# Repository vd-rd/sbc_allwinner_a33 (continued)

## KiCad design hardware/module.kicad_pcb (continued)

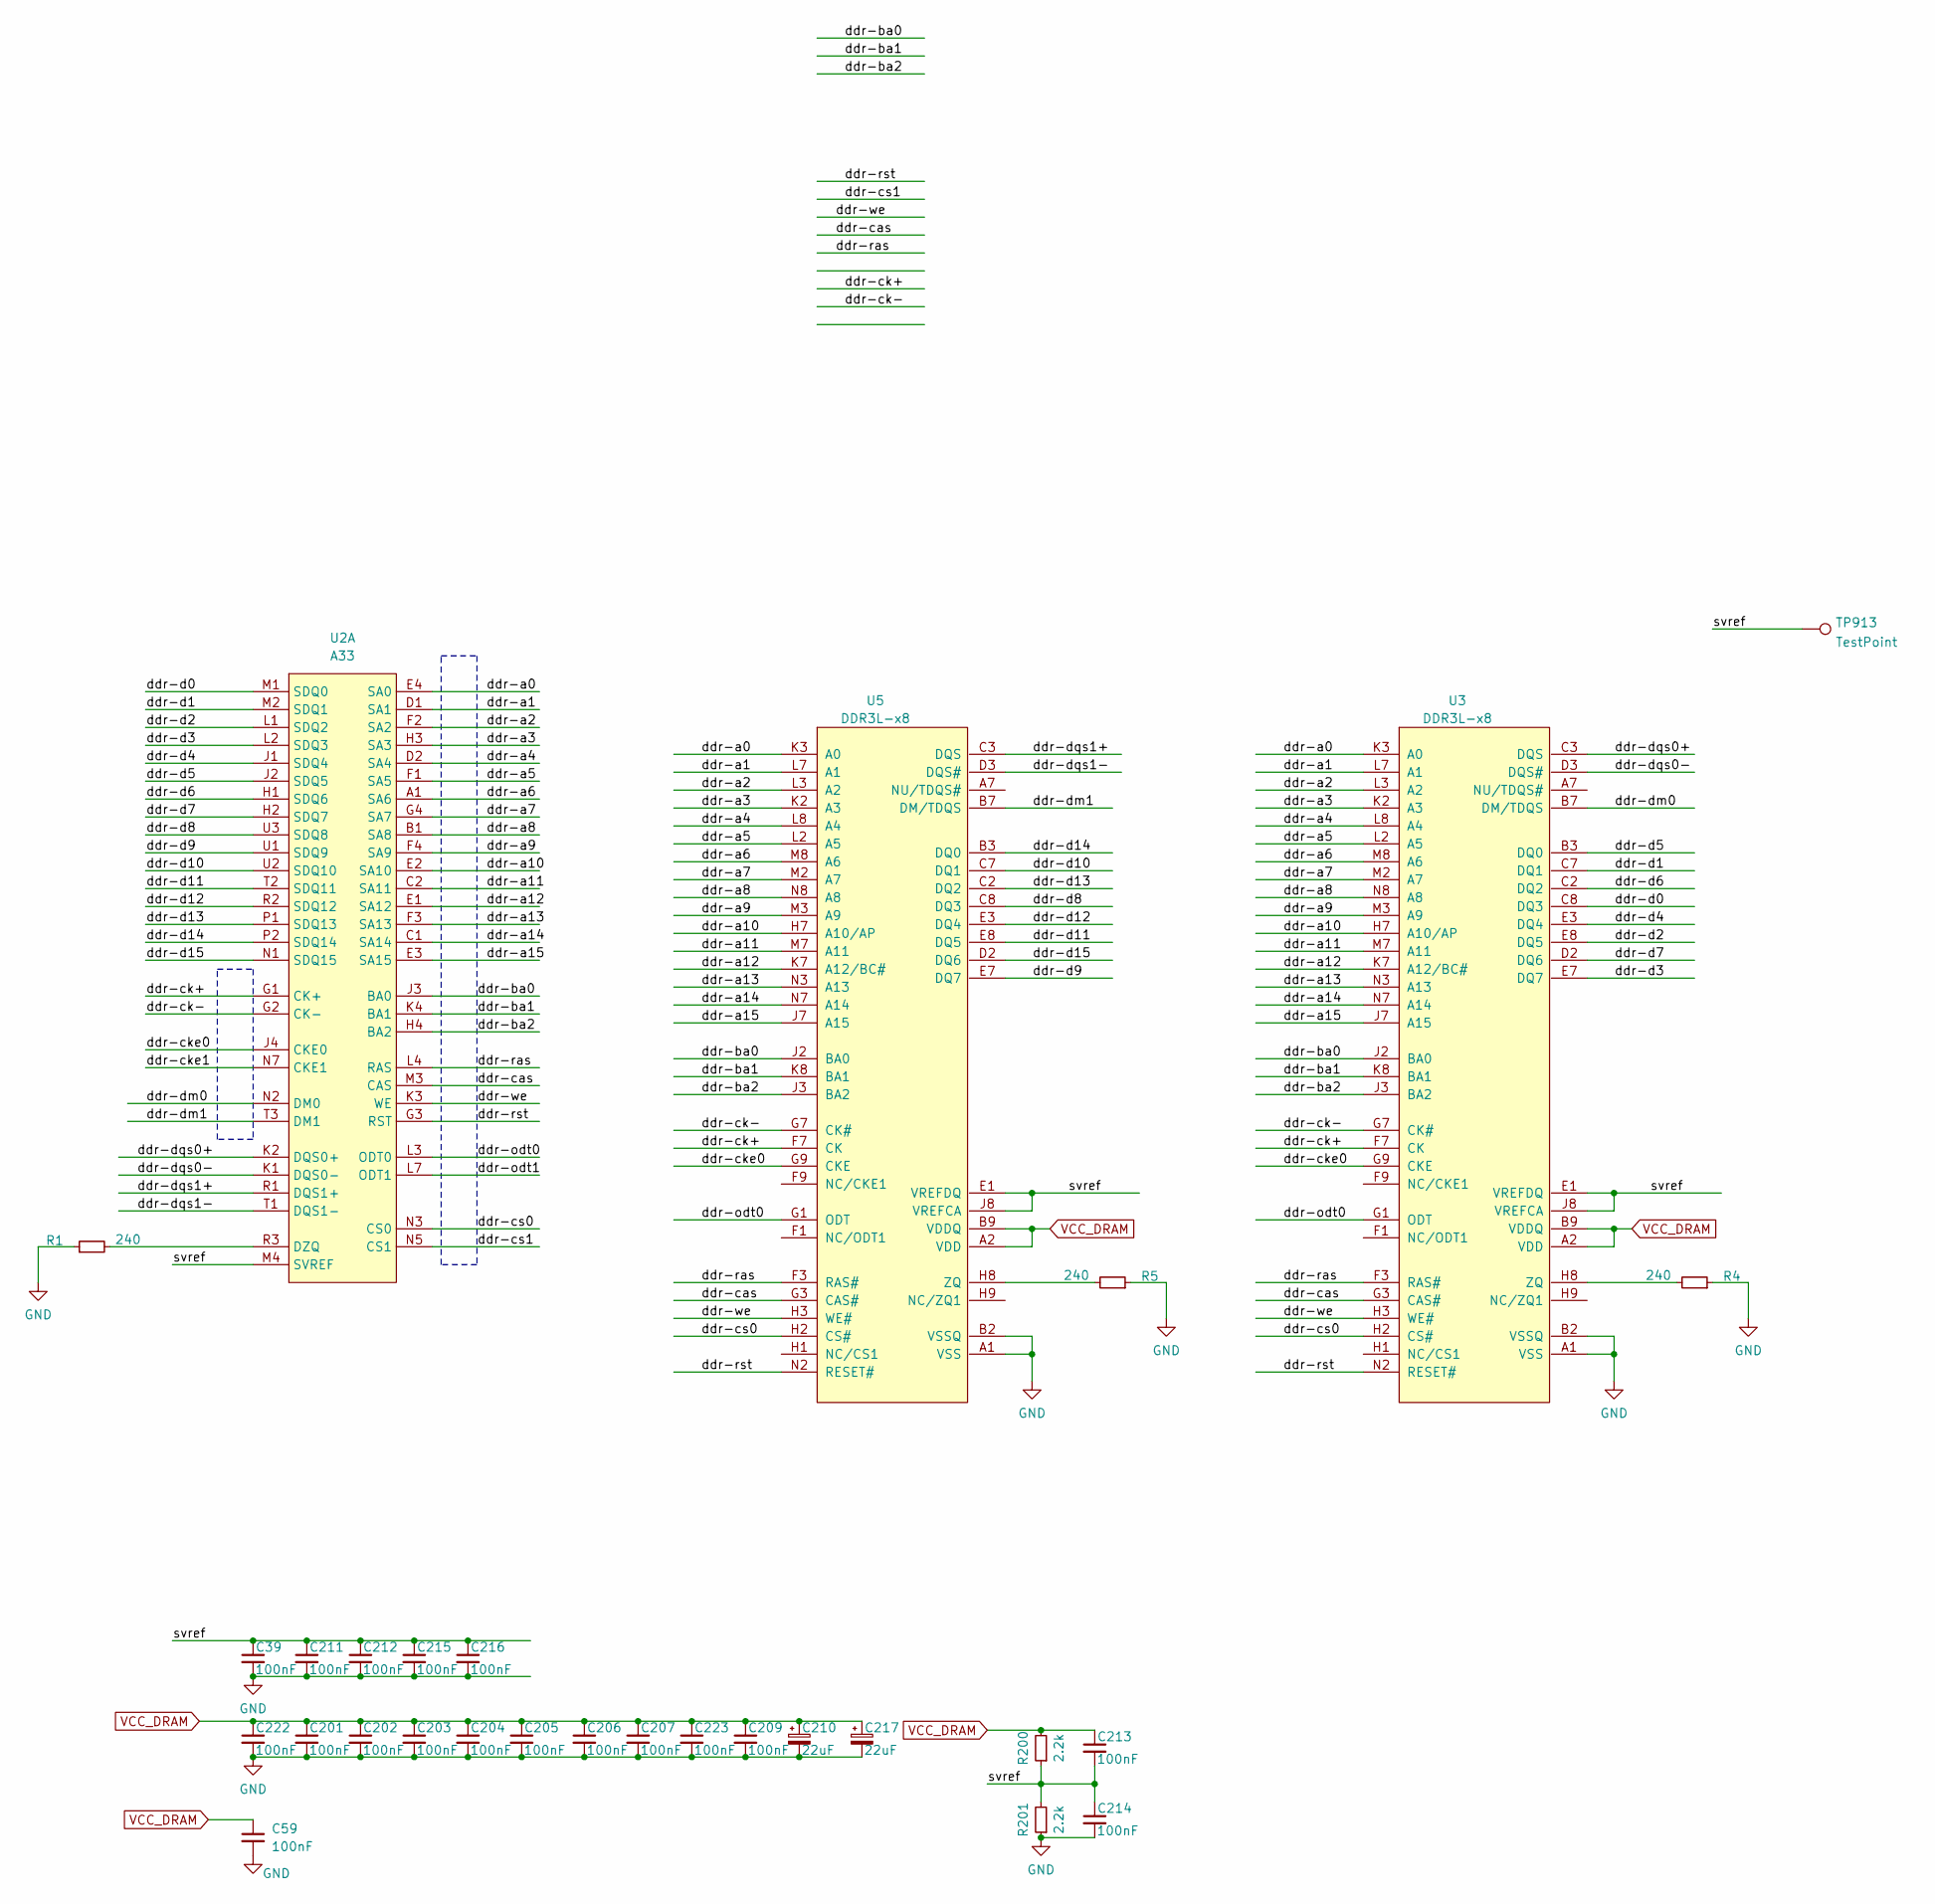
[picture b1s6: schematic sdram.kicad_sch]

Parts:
C39, C59, C201, C202, C203, C204, C205, C206, C207, C209, C211, C212, C213, C214, C215, C216, C222, C223: 100nF; C_0402_1005Metric
C210, C217: 22uF; CP_EIA-2012-15_AVX-P
R1, R4, R5: 240; R_0402_1005Metric
R200, R201: 2.2k; R_0402_1005Metric
TP913: TestPoint; TestPoint_Pad_D1.0mm
U2: A33; BGA-282_17x17_14.0x14.0mm
U3, U5: DDR3L-x8; BGA-78_9x13_9.0x10.5mm

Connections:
/DDR3 Memory/ddr-a0: U2.E4 (SA0), U3.K3 (A0), U5.K3 (A0)
/DDR3 Memory/ddr-a1: U2.D1 (SA1), U3.L7 (A1), U5.L7 (A1)
/DDR3 Memory/ddr-a2: U2.F2 (SA2), U3.L3 (A2), U5.L3 (A2)
/DDR3 Memory/ddr-a3: U2.H3 (SA3), U3.K2 (A3), U5.K2 (A3)
/DDR3 Memory/ddr-a4: U2.D2 (SA4), U3.L8 (A4), U5.L8 (A4)
/DDR3 Memory/ddr-a5: U2.F1 (SA5), U3.L2 (A5), U5.L2 (A5)
/DDR3 Memory/ddr-a6: U2.A1 (SA6), U3.M8 (A6), U5.M8 (A6)
/DDR3 Memory/ddr-a7: U2.G4 (SA7), U3.M2 (A7), U5.M2 (A7)
/DDR3 Memory/ddr-a8: U2.B1 (SA8), U3.N8 (A8), U5.N8 (A8)
/DDR3 Memory/ddr-a9: U2.F4 (SA9), U3.M3 (A9), U5.M3 (A9)
/DDR3 Memory/ddr-a10: U2.E2 (SA10), U3.H7 (A10/AP), U5.H7 (A10/AP)
/DDR3 Memory/ddr-a11: U2.C2 (SA11), U3.M7 (A11), U5.M7 (A11)
/DDR3 Memory/ddr-a12: U2.E1 (SA12), U3.K7 (A12/BC#), U5.K7 (A12/BC#)
/DDR3 Memory/ddr-a13: U2.F3 (SA13), U3.N3 (A13), U5.N3 (A13)
/DDR3 Memory/ddr-a14: U2.C1 (SA14), U3.N7 (A14), U5.N7 (A14)
/DDR3 Memory/ddr-a15: U2.E3 (SA15), U3.J7 (A15), U5.J7 (A15)
/DDR3 Memory/ddr-ba0: U2.J3 (BA0), U3.J2 (BA0), U5.J2 (BA0)
/DDR3 Memory/ddr-ba1: U2.K4 (BA1), U3.K8 (BA1), U5.K8 (BA1)
/DDR3 Memory/ddr-ba2: U2.H4 (BA2), U3.J3 (BA2), U5.J3 (BA2)
/DDR3 Memory/ddr-cas: U2.M3 (CAS), U3.G3 (CAS#), U5.G3 (CAS#)
/DDR3 Memory/ddr-ck+: U2.G1 (CK+), U3.F7 (CK), U5.F7 (CK)
/DDR3 Memory/ddr-ck-: U2.G2 (CK-), U3.G7 (CK#), U5.G7 (CK#)
/DDR3 Memory/ddr-cke0: U2.J4 (CKE0), U3.G9 (CKE), U5.G9 (CKE)
/DDR3 Memory/ddr-cke1: U2.N7 (CKE1)
/DDR3 Memory/ddr-cs0: U2.N3 (CS0), U3.H2 (CS#), U5.H2 (CS#)
/DDR3 Memory/ddr-cs1: U2.N5 (CS1)
/DDR3 Memory/ddr-d0: U2.M1 (SDQ0), U3.C8 (DQ3)
/DDR3 Memory/ddr-d1: U2.M2 (SDQ1), U3.C7 (DQ1)
/DDR3 Memory/ddr-d2: U2.L1 (SDQ2), U3.E8 (DQ5)
/DDR3 Memory/ddr-d3: U2.L2 (SDQ3), U3.E7 (DQ7)
/DDR3 Memory/ddr-d4: U2.J1 (SDQ4), U3.E3 (DQ4)
/DDR3 Memory/ddr-d5: U2.J2 (SDQ5), U3.B3 (DQ0)
/DDR3 Memory/ddr-d6: U2.H1 (SDQ6), U3.C2 (DQ2)
/DDR3 Memory/ddr-d7: U2.H2 (SDQ7), U3.D2 (DQ6)
/DDR3 Memory/ddr-d8: U2.U3 (SDQ8), U5.C8 (DQ3)
/DDR3 Memory/ddr-d9: U2.U1 (SDQ9), U5.E7 (DQ7)
/DDR3 Memory/ddr-d10: U2.U2 (SDQ10), U5.C7 (DQ1)
/DDR3 Memory/ddr-d11: U2.T2 (SDQ11), U5.E8 (DQ5)
/DDR3 Memory/ddr-d12: U2.R2 (SDQ12), U5.E3 (DQ4)
/DDR3 Memory/ddr-d13: U2.P1 (SDQ13), U5.C2 (DQ2)
/DDR3 Memory/ddr-d14: U2.P2 (SDQ14), U5.B3 (DQ0)
/DDR3 Memory/ddr-d15: U2.N1 (SDQ15), U5.D2 (DQ6)
/DDR3 Memory/ddr-dm0: U2.N2 (DM0), U3.B7 (DM/TDQS)
/DDR3 Memory/ddr-dm1: U2.T3 (DM1), U5.B7 (DM/TDQS)
/DDR3 Memory/ddr-dqs0+: U2.K2 (DQS0+), U3.C3 (DQS)
/DDR3 Memory/ddr-dqs0-: U2.K1 (DQS0-), U3.D3 (DQS#)
/DDR3 Memory/ddr-dqs1+: U2.R1 (DQS1+), U5.C3 (DQS)
/DDR3 Memory/ddr-dqs1-: U2.T1 (DQS1-), U5.D3 (DQS#)
/DDR3 Memory/ddr-odt0: U2.L3 (ODT0), U3.G1 (ODT), U5.G1 (ODT)
/DDR3 Memory/ddr-odt1: U2.L7 (ODT1)
/DDR3 Memory/ddr-ras: U2.L4 (RAS), U3.F3 (RAS#), U5.F3 (RAS#)
/DDR3 Memory/ddr-rst: U2.G3 (RST), U3.N2 (RESET#), U5.N2 (RESET#)
/DDR3 Memory/ddr-we: U2.K3 (WE), U3.H3 (WE#), U5.H3 (WE#)
/DDR3 Memory/svref: C39.1, C211.1, C212.1, C213.2, C214.1, C215.1, C216.1, R200.1, R201.2, TP913.1 (1_1), U2.M4 (SVREF), U3.E1 (VREFDQ), U3.J8 (VREFCA), U5.E1 (VREFDQ), U5.J8 (VREFCA)
GND: C39.2, C59.2, C201.2, C202.2, C203.2, C204.2, C205.2, C206.2, C207.2, C209.2, C210.2, C211.2, C212.2, C214.2, C215.2, C216.2, C217.2, C222.2, C223.2, R1.1, R4.1, R5.1, R201.1, U3.A1 (VSS), U3.A8 (VSS), U3.B1 (VSS), U3.B2 (VSSQ), U3.B8 (VSSQ), U3.C9 (VSSQ), U3.D1 (VSSQ), U3.D8 (VSS), U3.D9 (VSSQ), U3.F2 (VSS), U3.F8 (VSS), U3.J1 (VSS), U3.J9 (VSS), U3.L1 (VSS), U3.L9 (VSS), U3.N1 (VSS), U3.N9 (VSS), U5.A1 (VSS), U5.A8 (VSS), U5.B1 (VSS), U5.B2 (VSSQ), U5.B8 (VSSQ), U5.C9 (VSSQ), U5.D1 (VSSQ), U5.D8 (VSS), U5.D9 (VSSQ), U5.F2 (VSS), U5.F8 (VSS), U5.J1 (VSS), U5.J9 (VSS), U5.L1 (VSS), U5.L9 (VSS), U5.N1 (VSS), U5.N9 (VSS); also elsewhere on the board
unnamed: R1.2, U2.R3 (DZQ)
unnamed: R4.2, U3.H8 (ZQ)
unnamed: R5.2, U5.H8 (ZQ)
VCC_DRAM: C59.1, C201.1, C202.1, C203.1, C204.1, C205.1, C206.1, C207.1, C209.1, C210.1, C213.1, C217.1, C222.1, C223.1, R200.2, U3.A2 (VDD), U3.A9 (VDD), U3.B9 (VDDQ), U3.C1 (VDDQ), U3.D7 (VDD), U3.E2 (VDDQ), U3.E9 (VDDQ), U3.G2 (VDD), U3.G8 (VDD), U3.K1 (VDD), U3.K9 (VDD), U3.M1 (VDD), U3.M9 (VDD), U5.A2 (VDD), U5.A9 (VDD), U5.B9 (VDDQ), U5.C1 (VDDQ), U5.D7 (VDD), U5.E2 (VDDQ), U5.E9 (VDDQ), U5.G2 (VDD), U5.G8 (VDD), U5.K1 (VDD), U5.K9 (VDD), U5.M1 (VDD), U5.M9 (VDD); also elsewhere on the board

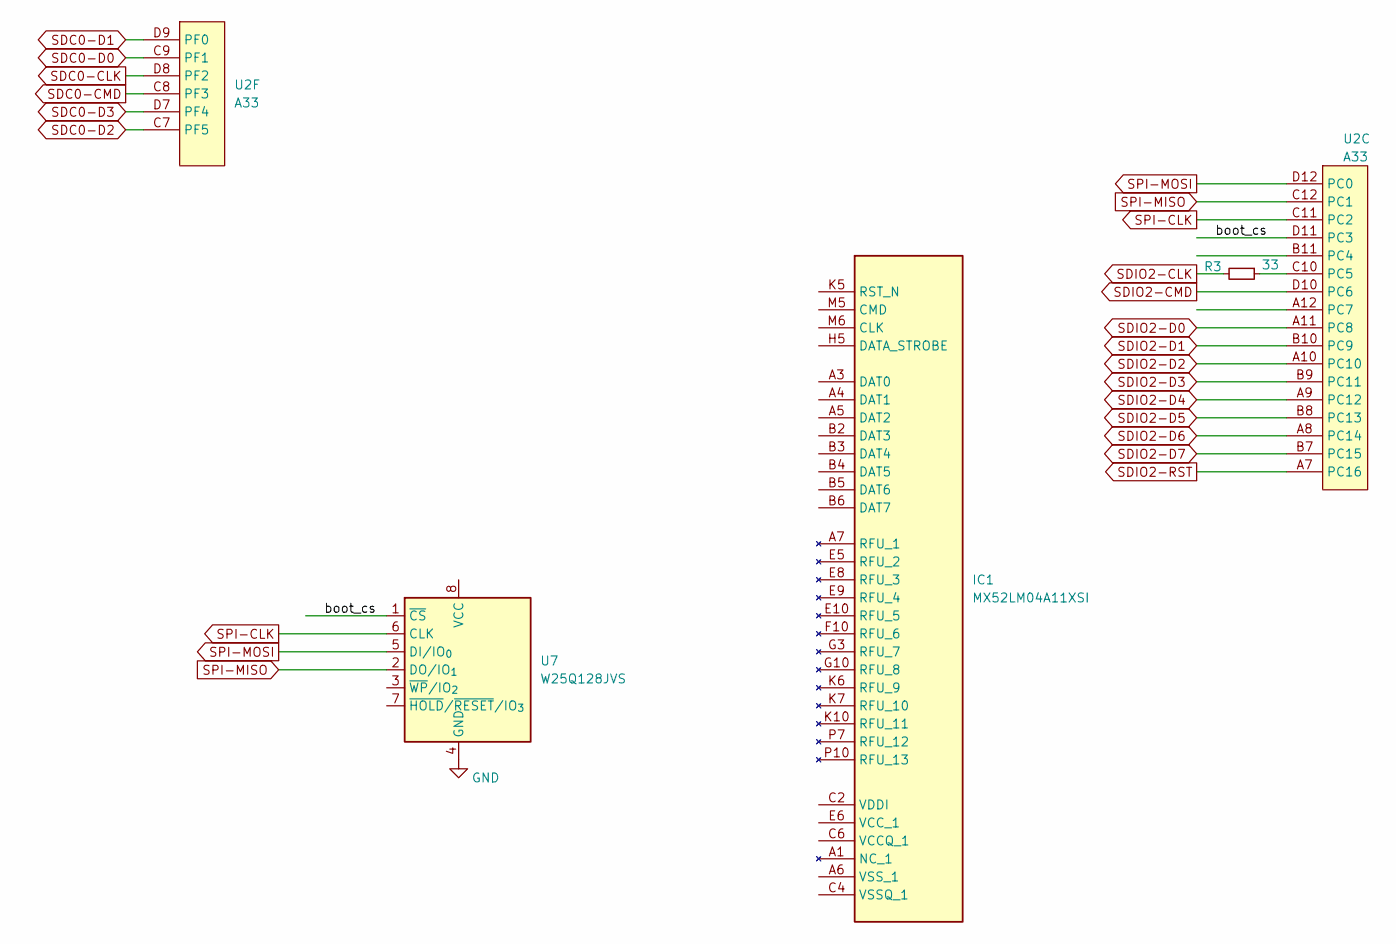
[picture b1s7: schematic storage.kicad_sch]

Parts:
IC1: MX52LM04A11XSI; BGA153C50P14X14_1150X1300X80; Mouser Part Number 95-52LM04A11XSIT
R3: 33; R_0402_1005Metric
U2: A33; BGA-282_17x17_14.0x14.0mm
U7: W25Q128JVS; SOIC-8_5.3x5.3mm_P1.27mm

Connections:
/Storage/boot_cs: U2.D11 (PC3), U7.1 (~CS)
GND: U7.4 (GND); also elsewhere on the board
unnamed: IC1.C6 (VCCQ_1), IC1.M4 (VCCQ_2), IC1.N4 (VCCQ_3), IC1.P3 (VCCQ_4), IC1.P5 (VCCQ_5)
unnamed: IC1.E6 (VCC_1), IC1.F5 (VCC_2), IC1.J10 (VCC_3), IC1.K9 (VCC_4)
unnamed: IC1.C4 (VSSQ_1), IC1.N2 (VSSQ_2), IC1.N5 (VSSQ_3), IC1.P4 (VSSQ_4), IC1.P6 (VSSQ_5)
unnamed: IC1.A6 (VSS_1), IC1.E7 (VSS_2), IC1.G5 (VSS_3), IC1.H10 (VSS_4), IC1.J5 (VSS_5), IC1.K8 (VSS_6)
unnamed: R3.1, U2.C10 (PC5)
SDC0-CLK: U2.D8 (PF2); also elsewhere on the board
SDC0-CMD: U2.C8 (PF3); also elsewhere on the board
SDC0-D0: U2.C9 (PF1); also elsewhere on the board
SDC0-D1: U2.D9 (PF0); also elsewhere on the board
SDC0-D2: U2.C7 (PF5); also elsewhere on the board
SDC0-D3: U2.D7 (PF4); also elsewhere on the board
SDIO2-CLK: R3.2
SDIO2-CMD: U2.D10 (PC6)
SDIO2-D0: U2.A11 (PC8)
SDIO2-D1: U2.B10 (PC9)
SDIO2-D2: U2.A10 (PC10)
SDIO2-D3: U2.B9 (PC11)
SDIO2-D4: U2.A9 (PC12)
SDIO2-D5: U2.B8 (PC13)
SDIO2-D6: U2.A8 (PC14)
SDIO2-D7: U2.B7 (PC15)
SDIO2-RST: U2.A7 (PC16)
SPI-CLK: U2.C11 (PC2), U7.6 (CLK); also elsewhere on the board
SPI-MISO: U2.C12 (PC1), U7.2 (DO/IO_{1}); also elsewhere on the board
SPI-MOSI: U2.D12 (PC0), U7.5 (DI/IO_{0}); also elsewhere on the board

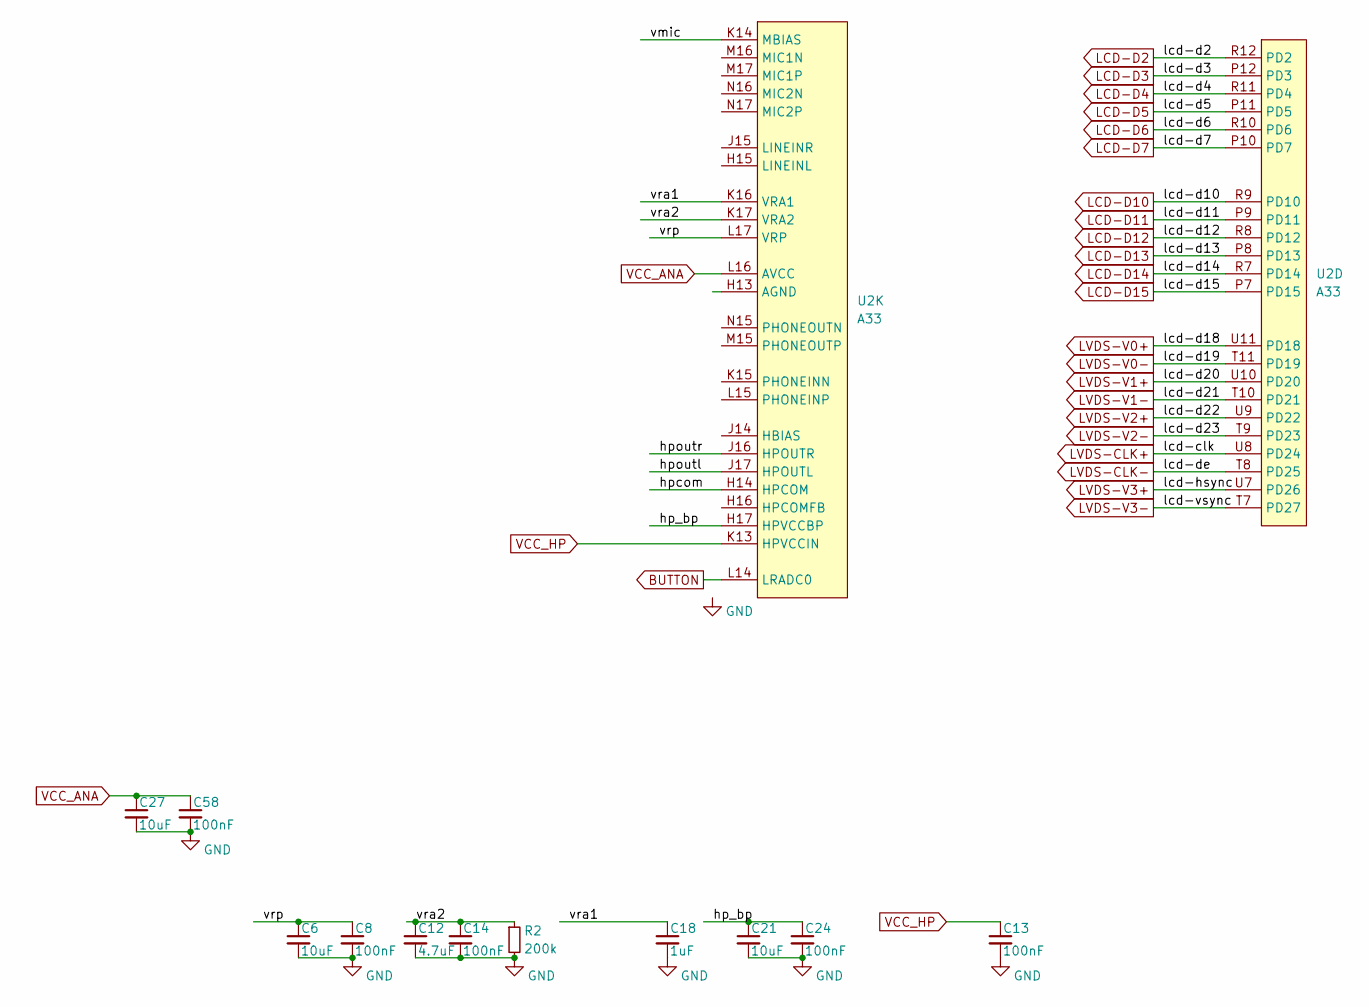
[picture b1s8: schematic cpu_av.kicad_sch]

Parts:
C6, C21, C27: 10uF; C_0603_1608Metric
C8, C13, C14, C24, C58: 100nF; C_0402_1005Metric
C12: 4.7uF; C_0603_1608Metric
C18: 1uF; C_0402_1005Metric
R2: 200k; R_0402_1005Metric
U2: A33; BGA-282_17x17_14.0x14.0mm

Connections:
/AudioVideo/hp_bp: C21.1, C24.1, U2.H17 (HPVCCBP)
/AudioVideo/hpcom: U2.H14 (HPCOM)
/AudioVideo/hpoutl: U2.J17 (HPOUTL)
/AudioVideo/hpoutr: U2.J16 (HPOUTR)
/AudioVideo/vmic: U2.K14 (MBIAS)
/AudioVideo/vra1: C18.1, U2.K16 (VRA1)
/AudioVideo/vra2: C12.1, C14.1, R2.1, U2.K17 (VRA2)
/AudioVideo/vrp: C6.1, C8.1, U2.L17 (VRP)
BUTTON: U2.L14 (LRADC0); also elsewhere on the board
GND: C6.2, C8.2, C12.2, C13.2, C14.2, C18.2, C21.2, C24.2, C27.2, C58.2, R2.2; also elsewhere on the board
LCD-D2: U2.R12 (PD2); also elsewhere on the board
LCD-D3: U2.P12 (PD3); also elsewhere on the board
LCD-D4: U2.R11 (PD4); also elsewhere on the board
LCD-D5: U2.P11 (PD5); also elsewhere on the board
LCD-D6: U2.R10 (PD6); also elsewhere on the board
LCD-D7: U2.P10 (PD7); also elsewhere on the board
LCD-D10: U2.R9 (PD10); also elsewhere on the board
LCD-D11: U2.P9 (PD11); also elsewhere on the board
LCD-D12: U2.R8 (PD12); also elsewhere on the board
LCD-D13: U2.P8 (PD13); also elsewhere on the board
LCD-D14: U2.R7 (PD14); also elsewhere on the board
LCD-D15: U2.P7 (PD15); also elsewhere on the board
LVDS-CLK+: U2.U8 (PD24); also elsewhere on the board
LVDS-CLK-: U2.T8 (PD25); also elsewhere on the board
LVDS-V0+: U2.U11 (PD18); also elsewhere on the board
LVDS-V0-: U2.T11 (PD19); also elsewhere on the board
LVDS-V1+: U2.U10 (PD20); also elsewhere on the board
LVDS-V1-: U2.T10 (PD21); also elsewhere on the board
LVDS-V2+: U2.U9 (PD22); also elsewhere on the board
LVDS-V2-: U2.T9 (PD23); also elsewhere on the board
LVDS-V3+: U2.U7 (PD26); also elsewhere on the board
LVDS-V3-: U2.T7 (PD27); also elsewhere on the board
VCC_ANA: C27.1, C58.1, U2.L16 (AVCC); also elsewhere on the board
VCC_HP: C13.1, U2.K13 (HPVCCIN)

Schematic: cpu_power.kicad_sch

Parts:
C5, C9, C10, C11, C32, C34, C41, C52, C53, C56: 100nF; C_0402_1005Metric
C15, C17, C19, C20: 4.7uF; C_0402_1005Metric
C16, C22, C23, C25, C26, C42, C49, C50, C51: 1uF; C_0402_1005Metric
C30, C40, C55: 100nF; C_0201_0603Metric
C54: 1nF; C_0402_1005Metric
U2: A33; BGA-282_17x17_14.0x14.0mm

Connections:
/CPU Power/rtcvio: C19.1, U2.M13 (RTCVIO)
GND: C5.2, C9.2, C10.2, C11.2, C15.2, C16.2, C17.2, C19.2, C20.2, C22.2, C23.2, C25.2, C26.2, C30.2, C32.2, C34.2, C40.2, C41.2, C42.2, C49.2, C50.2, C51.2, C52.2, C53.2, C54.2, C55.2, C56.2, U2.F8 (GND), U2.F9 (GND), U2.F10 (GND), U2.G7 (GND), U2.G8 (GND), U2.G9 (GND), U2.G10 (GND), U2.G11 (GND), U2.H7 (GND), U2.H8 (GND), U2.H9 (GND), U2.H10 (GND), U2.H11 (GND), U2.H12 (GND), U2.J7 (GND), U2.J8 (GND), U2.J9 (GND), U2.J10 (GND), U2.J11 (GND), U2.J12 (GND), U2.K7 (GND), U2.K8 (GND), U2.K9 (GND), U2.K10 (GND), U2.K11 (GND), U2.K12 (GND), U2.L8 (GND), U2.L9 (GND), U2.L10 (GND), U2.L11 (GND), U2.M8 (VCC-EFUSE), U2.M9 (GND), U2.M10 (GND), U2.N4 (GND); also elsewhere on the board
VCC_CORE: C20.1, C23.1, C26.1, C52.1, C53.1, C54.1, U2.E5 (VDD-CPU), U2.E6 (VDD-CPU), U2.E7 (VDD-CPU), U2.F5 (VDD-CPU), U2.F6 (VDD-CPU), U2.F7 (VDD-CPU), U2.G5 (VDD-CPU), U2.G6 (VDD-CPU); also elsewhere on the board
VCC_CPUS: C56.1, U2.M14 (VDD-CPUS); also elsewhere on the board
VCC_DLL: C11.1, U2.P3 (VDD-DLL); also elsewhere on the board
VCC_DRAM: C9.1, C10.1, C16.1, C17.1, U2.H5 (VCC-DRAM), U2.H6 (VCC-DRAM), U2.J5 (VCC-DRAM), U2.J6 (VCC-DRAM), U2.K5 (VCC-DRAM), U2.L5 (VCC-DRAM); also elsewhere on the board
VCC_DSI: C40.1, U2.N6 (VCC-DSI)
VCC_INT: C15.1, C22.1, C25.1, C32.1, C34.1, U2.E8 (VDD-SYS), U2.E9 (VDD-SYS), U2.E10 (VDD-SYS), U2.K6 (VDD-SYS), U2.L6 (VDD-SYS), U2.M6 (VDD-SYS), U2.M7 (VDD-SYS), U2.N8 (VDD-SYS), U2.N9 (VDD-SYS), U2.N10 (VDD-SYS), U2.N12 (VCC-HSIC); also elsewhere on the board
VCC_IO: C42.1, C49.1, C50.1, C51.1, U2.E11 (VCC-IO), U2.E12 (VCC-IO), U2.F11 (VCC-IO), U2.F12 (VCC-IO), U2.G12 (VCC-IO); also elsewhere on the board
VCC_PD: C41.1, U2.M11 (VCC-PD), U2.N11 (VCC-PD)
VCC_PLL: C55.1, U2.M5 (VCC-PLL)
VCC_RTC: C30.1, U2.M12 (VCC-RTC)
VCC_USB: C5.1, U2.L12 (VCC-USB)

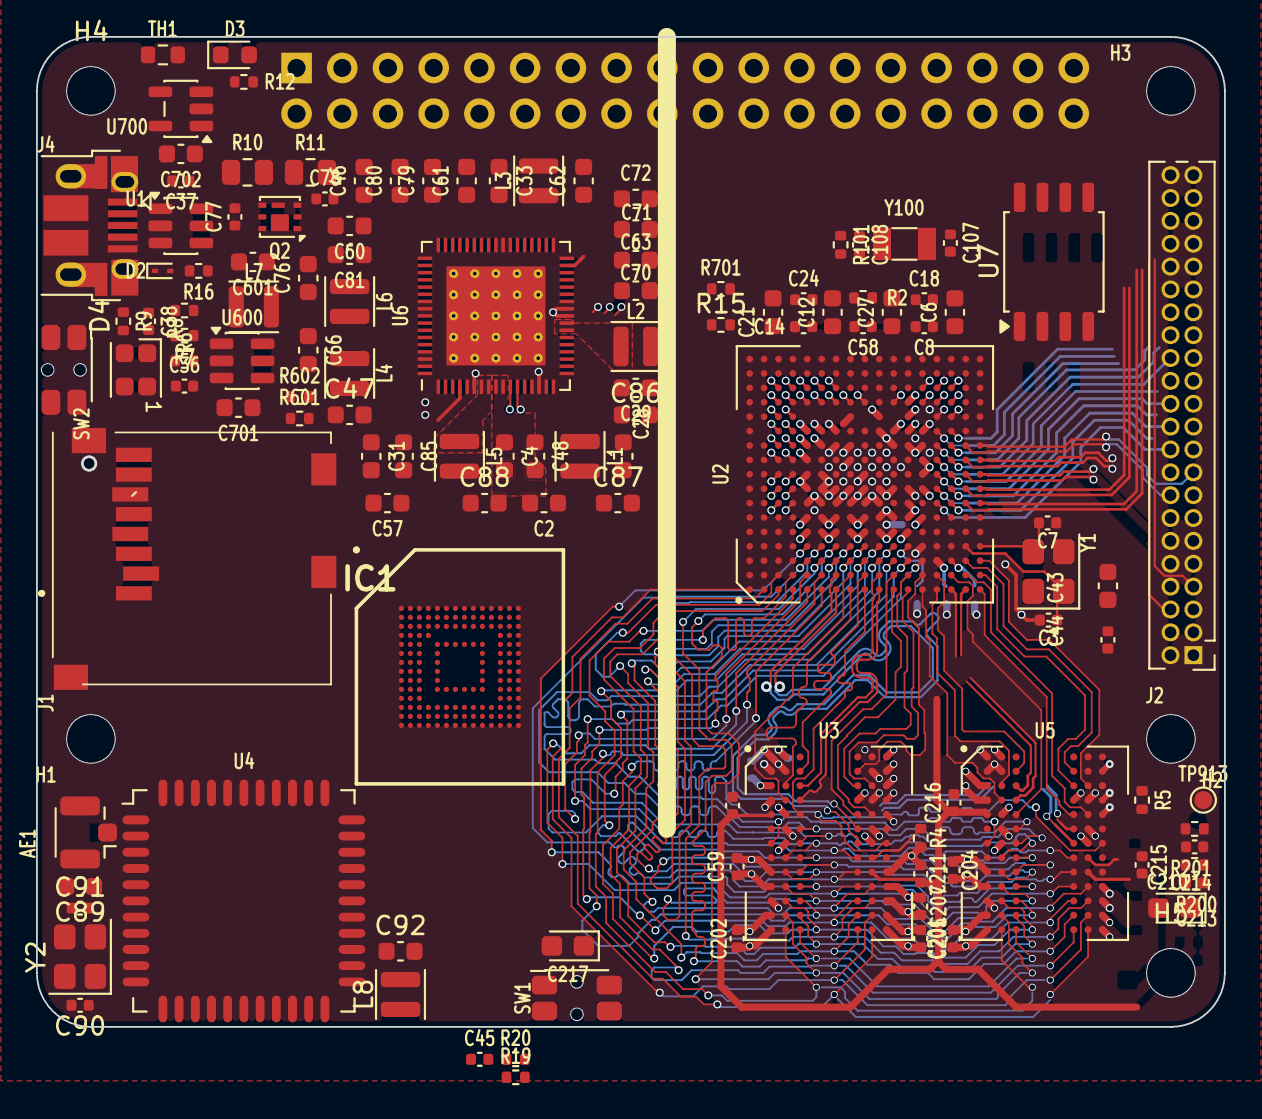
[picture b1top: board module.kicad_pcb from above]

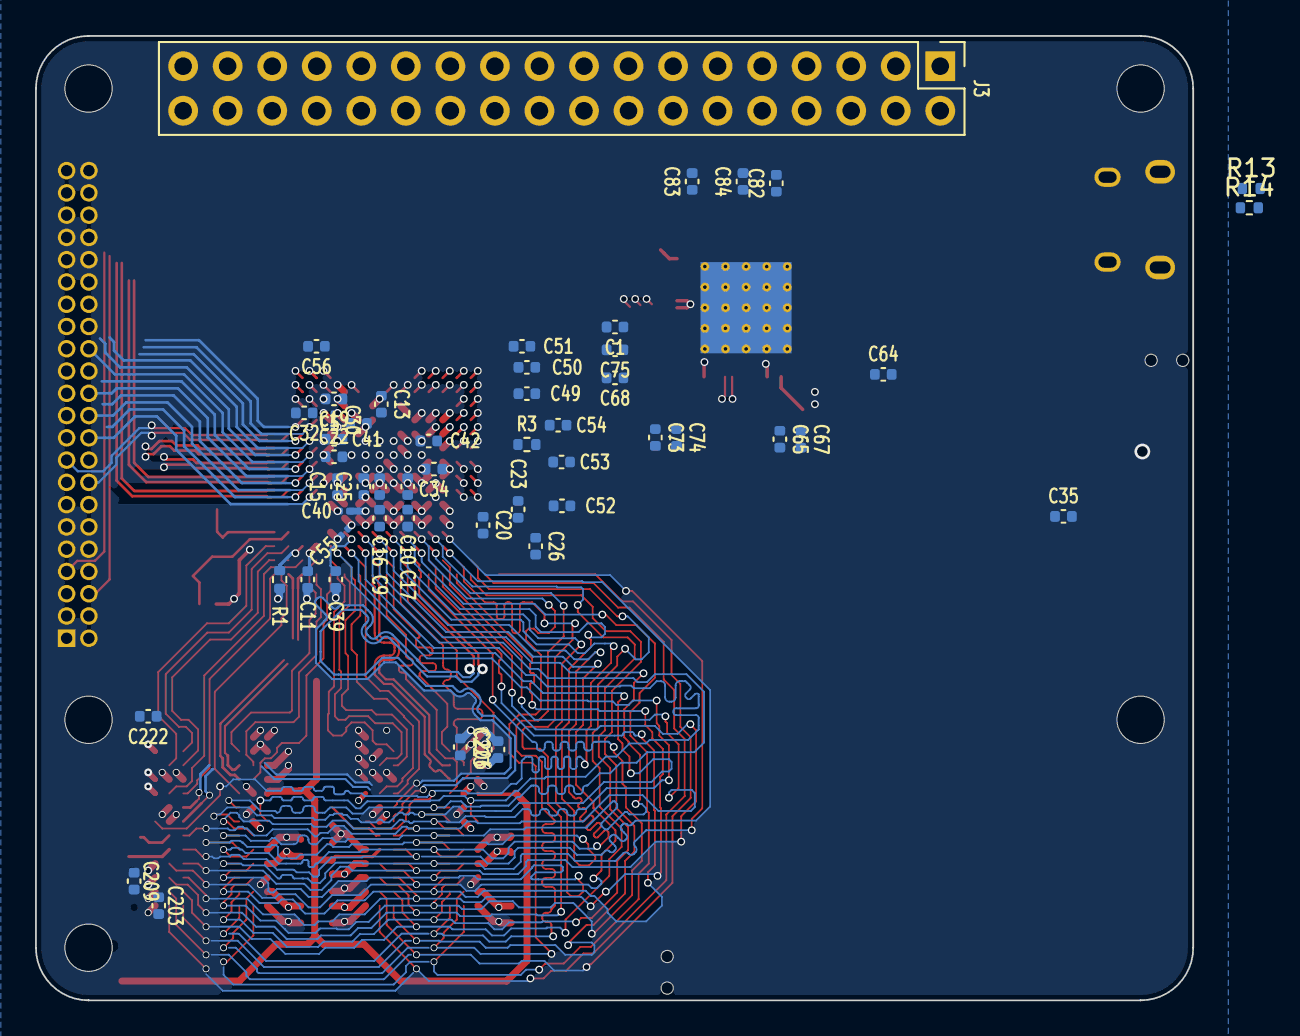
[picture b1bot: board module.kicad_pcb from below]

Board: 4 copper layers, 66.0 x 55.0 mm, 177 parts (51 on the bottom side), 206 nets.

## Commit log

2026-01-15 basic hardware layout
2026-01-26 updated board layout
2026-01-26 fix board outline
2026-02-05 small routing work
2026-05-03 updated gitignore
2026-05-04 bump to kicad 10
2026-05-05 defined cpu connections
2026-05-08 more routing and feature defs
2026-06-30 project updates
